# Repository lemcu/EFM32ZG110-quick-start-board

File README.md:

EFM32ZG110-quick-start-board
============================
This board is designed to be used with [LemcUSB](https://github.com/lemcu/LemcUSB), a purely software based USB peripheral for ARM Cortex M0+ devices.

Zero Gecko 110 quick start breakout board features:

1. USB support using [LemcUSB](https://github.com/lemcu/LemcUSB)
2. 31mm X 23.3mm sized board.
3. Can use either through-hole or SMD High Frequency crystal.
4. Footprint to mount an optional inductor between AVDD and VDD for Analog intensive application.
5. On board SWD Connector.
6. Onboard low noise 3.3V LDO.
7. ESD protection diodes on USB D+ D- lines.

EFM32ZG110 is chosen for presence of onchip ADC instead of EFM32ZG108.

<br />This work is licensed under a <a rel="license" href="http://creativecommons.org/licenses/by-sa/3.0/deed.en_US">Creative Commons Attribution-ShareAlike 3.0 Unported License</a>.

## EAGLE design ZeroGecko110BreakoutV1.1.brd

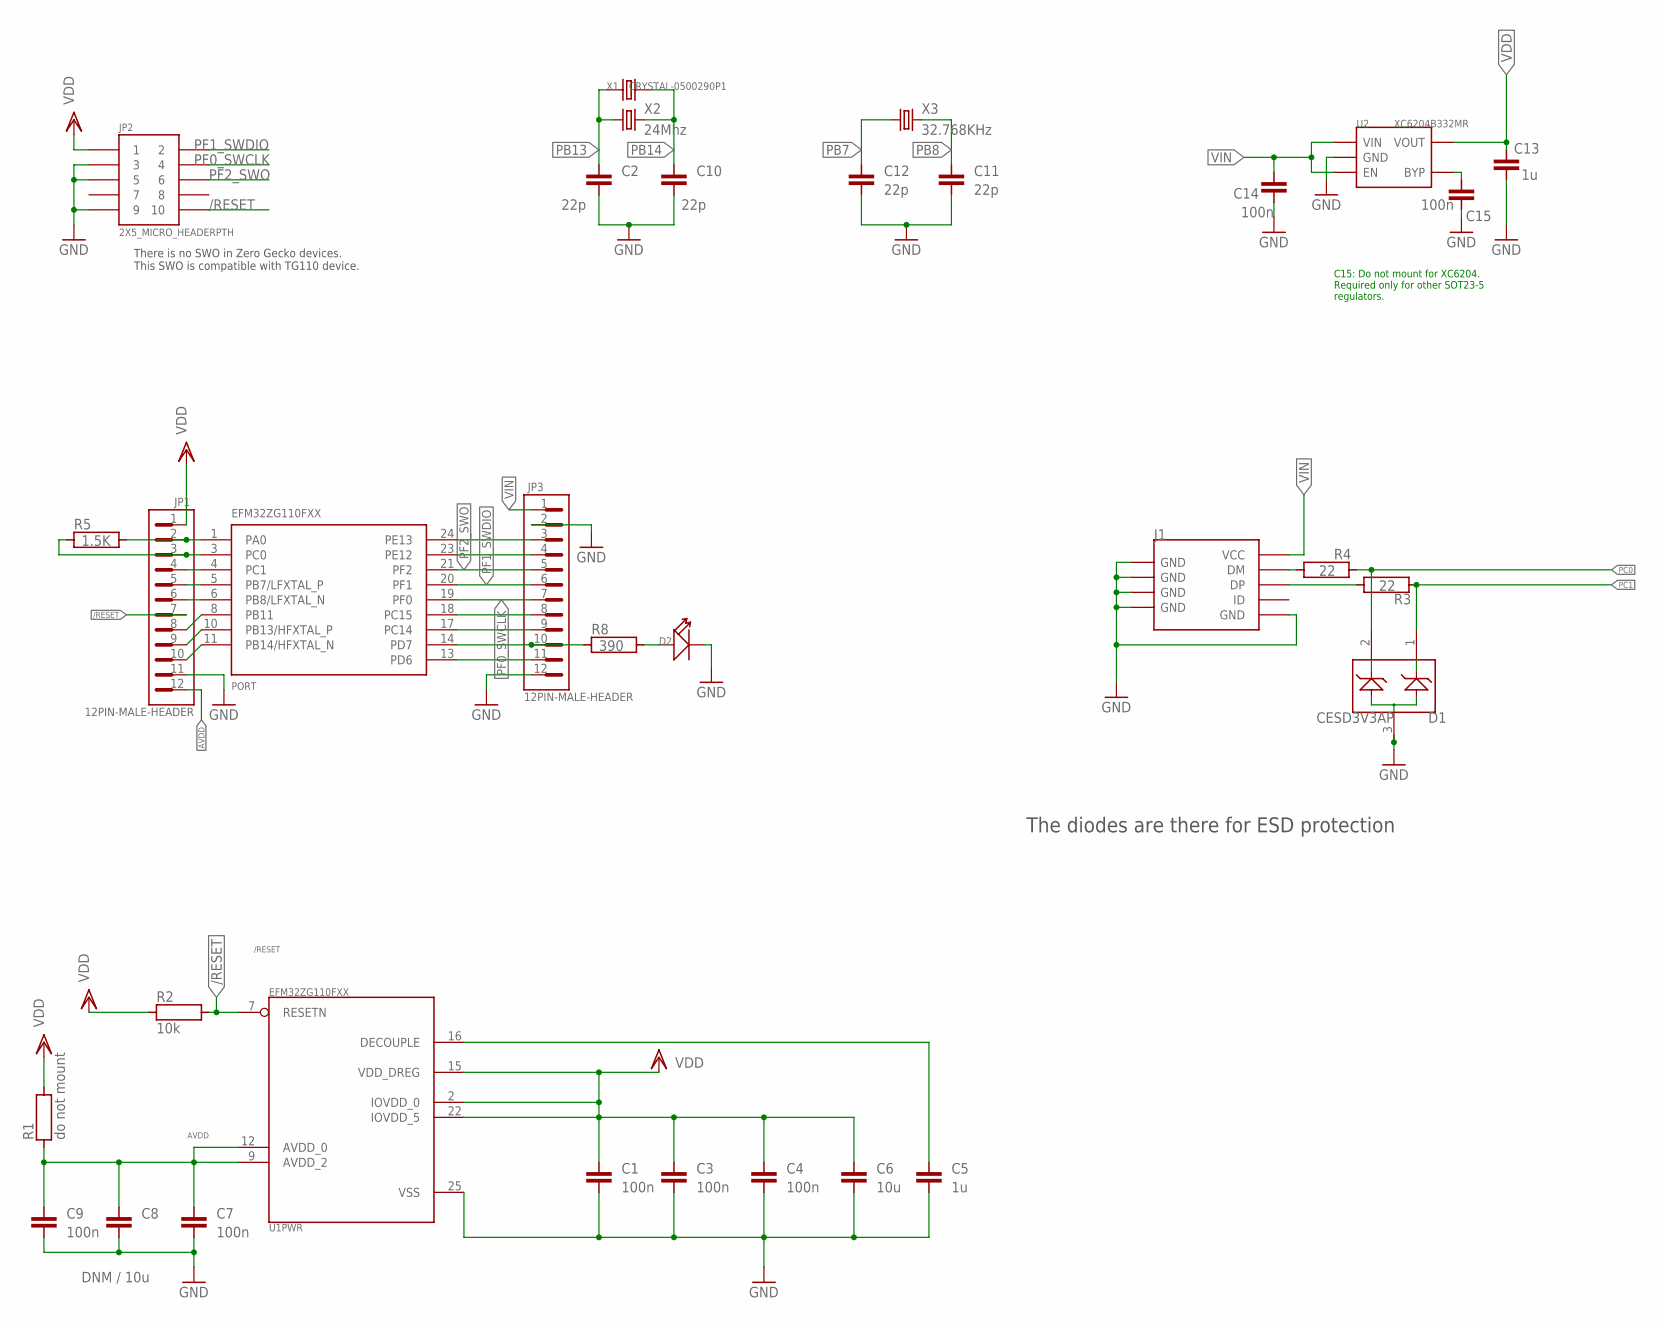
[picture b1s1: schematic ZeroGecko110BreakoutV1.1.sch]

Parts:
C1, C3, C4, C7, C9: 100n; C0603
C2, C10, C11, C12: 22p; C0603
C5, C13: 1u; C0805
C6: 10u; C0805
C8: DNM / 10u; C0805
C14, C15: 100n; C0805
D1: CESD3V3AP; SOT23
D2: LED; LED0603
J1: USB-MINIUSB-5P-MICRO; MICRO-USB
JP1, JP3: 12PIN-MALE-HEADER; 12P-2.54MM
JP2: 2X5_MICRO_HEADERPTH; 2X5_1.27MM_PTH
R1: do not mount; R0805
R2: 10k; R0603
R3, R4: 22; R0603
R5: 1.5K; R0603
R8: 390; R0603
U1: EFM32ZG110FXX; QFN24
U2: XC6204B332MR; SOT23-5
X1: CRYSTAL-0500290P1; 2P-SMD-5.0X3.2
X2: 24Mhz; HC49U-V
X3: 32.768KHz; TC26V

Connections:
/RESET: JP1.7, JP2.10, R2.2, U1.7 (RESETN)
AVDD: C7.2, C8.2, C9.2, JP1.12, R1.1, U1.9 (AVDD_2), U1.12 (AVDD_0)
GND: C1.1, C2.1, C3.1, C4.1, C5.1, C6.1, C7.1, C8.1, C9.1, C10.1, C11.1, C12.1, C13.1, C14.1, C15.1, D1.3, D2.-, J1.5 (GND), J1.S1 (GND), J1.S2 (GND), J1.S3 (GND), J1.S4 (GND), J1.S5 (GND), J1.S6 (GND), JP1.11, JP2.3, JP2.5, JP2.9, JP3.2, JP3.12, U1.25 (VSS), U2.2 (GND)
unnamed: J1.2 (DM), R4.1
unnamed: J1.3 (DP), R3.1
unnamed: D2.+, R8.2
unnamed: C15.2, U2.4 (BYP)
unnamed: C5.2, U1.16 (DECOUPLE)
PA0: JP1.2, R5.2, U1.1 (PA0)
PB7: C12.2, JP1.5, U1.5 (PB7/LFXTAL_P), X3.1
PB8: C11.2, JP1.6, U1.6 (PB8/LFXTAL_N), X3.2
PB11: JP1.8, U1.8 (PB11)
PB13: C2.2, JP1.9, U1.10 (PB13/HFXTAL_P), X1.1, X2.1
PB14: C10.2, JP1.10, U1.11 (PB14/HFXTAL_N), X1.2, X2.2
PC0: D1.2, JP1.3, R4.2, R5.1, U1.3 (PC0)
PC1: D1.1, JP1.4, R3.2, U1.4 (PC1)
PC14: JP3.9, U1.17 (PC14)
PC15: JP3.8, U1.18 (PC15)
PD6: JP3.11, U1.13 (PD6)
PD7: JP3.10, R8.1, U1.14 (PD7)
PE12: JP3.4, U1.23 (PE12)
PE13: JP3.3, U1.24 (PE13)
PF0_SWCLK: JP2.4, JP3.7, U1.19 (PF0)
PF1_SWDIO: JP2.2, JP3.6, U1.20 (PF1)
PF2_SWO: JP2.6, JP3.5, U1.21 (PF2)
VDD: C1.2, C3.2, C4.2, C6.2, C13.2, JP1.1, JP2.1, R1.2, R2.1, U1.2 (IOVDD_0), U1.15 (VDD_DREG), U1.22 (IOVDD_5), U2.5 (VOUT)
VIN: C14.2, J1.1 (VCC), JP3.1, U2.1 (VIN), U2.3 (EN)

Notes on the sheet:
There is no SWO in Zero Gecko devices. This SWO is compatible with TG110 device.
C15: Do not mount for XC6204. Required only for other SOT23-5 regulators.
The diodes are there for ESD protection

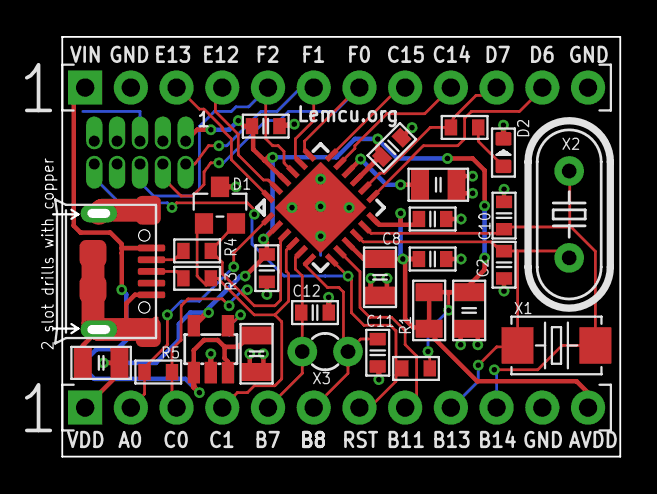
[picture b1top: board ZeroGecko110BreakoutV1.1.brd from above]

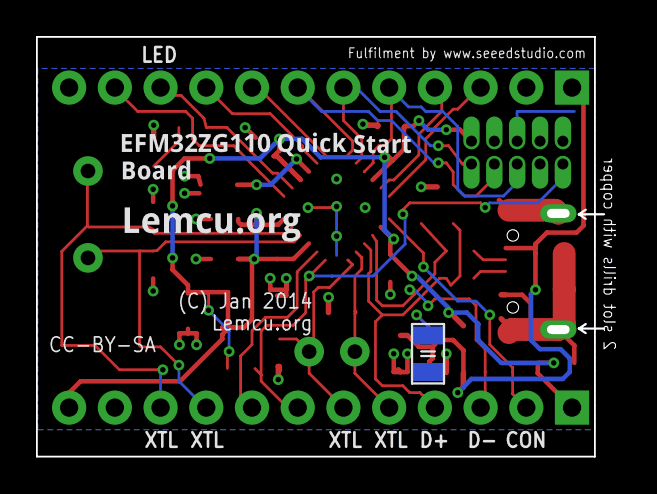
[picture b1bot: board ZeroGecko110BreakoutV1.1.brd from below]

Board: 2 copper layers, 32.0 x 22.9 mm, 32 parts (2 on the bottom side), 27 nets.

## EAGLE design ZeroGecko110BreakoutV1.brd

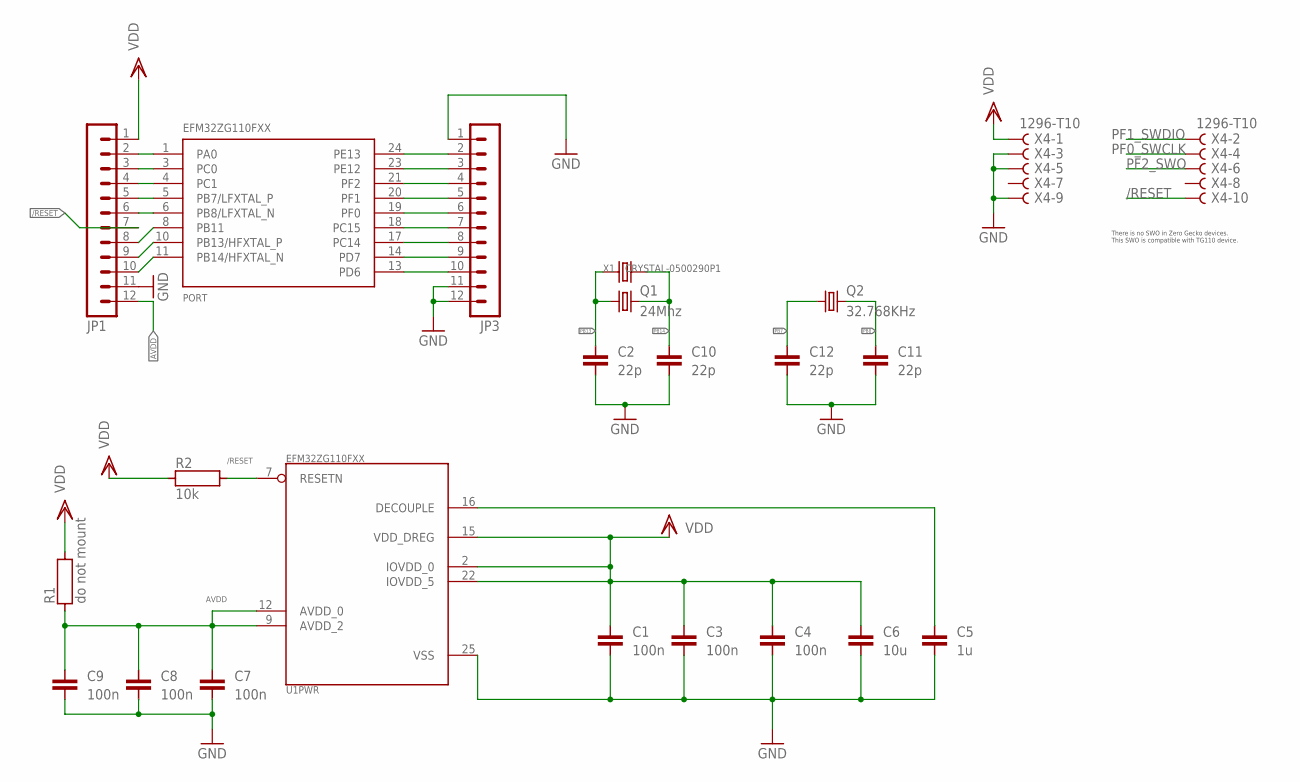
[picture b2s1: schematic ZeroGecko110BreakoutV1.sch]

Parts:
C1, C3, C4, C7, C8, C9: 100n; C0603
C2, C10, C11, C12: 22p; C0603
C5: 1u; C0805
C6: 10u; C0805
JP1, JP3: MA12-1
Q1: 24Mhz; HC49U-V
Q2: 32.768KHz; TC26V
R1: do not mount; R0805
R2: 10k; R0603
U1: EFM32ZG110FXX; QFN24
X1: CRYSTAL-0500290P1; 2P-SMD-5.0X3.2
X4: 1296-T10; 1296-10

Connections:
/RESET: JP1.7, R2.2, U1.7 (RESETN), X4.10
AVDD: C7.2, C8.2, C9.2, JP1.12, R1.1, U1.9 (AVDD_2), U1.12 (AVDD_0)
GND: C1.1, C2.1, C3.1, C4.1, C5.1, C6.1, C7.1, C8.1, C9.1, C10.1, C11.1, C12.1, JP1.11, JP3.1, JP3.11, JP3.12, U1.25 (VSS), X4.3, X4.5, X4.9
unnamed: C5.2, U1.16 (DECOUPLE)
PA0: JP1.2, U1.1 (PA0)
PB7: C12.2, JP1.5, Q2.1, U1.5 (PB7/LFXTAL_P)
PB8: C11.2, JP1.6, Q2.2, U1.6 (PB8/LFXTAL_N)
PB11: JP1.8, U1.8 (PB11)
PB13: C2.2, JP1.9, Q1.1, U1.10 (PB13/HFXTAL_P), X1.1
PB14: C10.2, JP1.10, Q1.2, U1.11 (PB14/HFXTAL_N), X1.2
PC0: JP1.3, U1.3 (PC0)
PC1: JP1.4, U1.4 (PC1)
PC14: JP3.8, U1.17 (PC14)
PC15: JP3.7, U1.18 (PC15)
PD6: JP3.10, U1.13 (PD6)
PD7: JP3.9, U1.14 (PD7)
PE12: JP3.3, U1.23 (PE12)
PE13: JP3.2, U1.24 (PE13)
PF0_SWCLK: JP3.6, U1.19 (PF0), X4.4
PF1_SWDIO: JP3.5, U1.20 (PF1), X4.2
PF2_SWO: JP3.4, U1.21 (PF2), X4.6
VDD: C1.2, C3.2, C4.2, C6.2, JP1.1, R1.2, R2.1, U1.2 (IOVDD_0), U1.15 (VDD_DREG), U1.22 (IOVDD_5), X4.1

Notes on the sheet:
There is no SWO in Zero Gecko devices. This SWO is compatible with TG110 device.

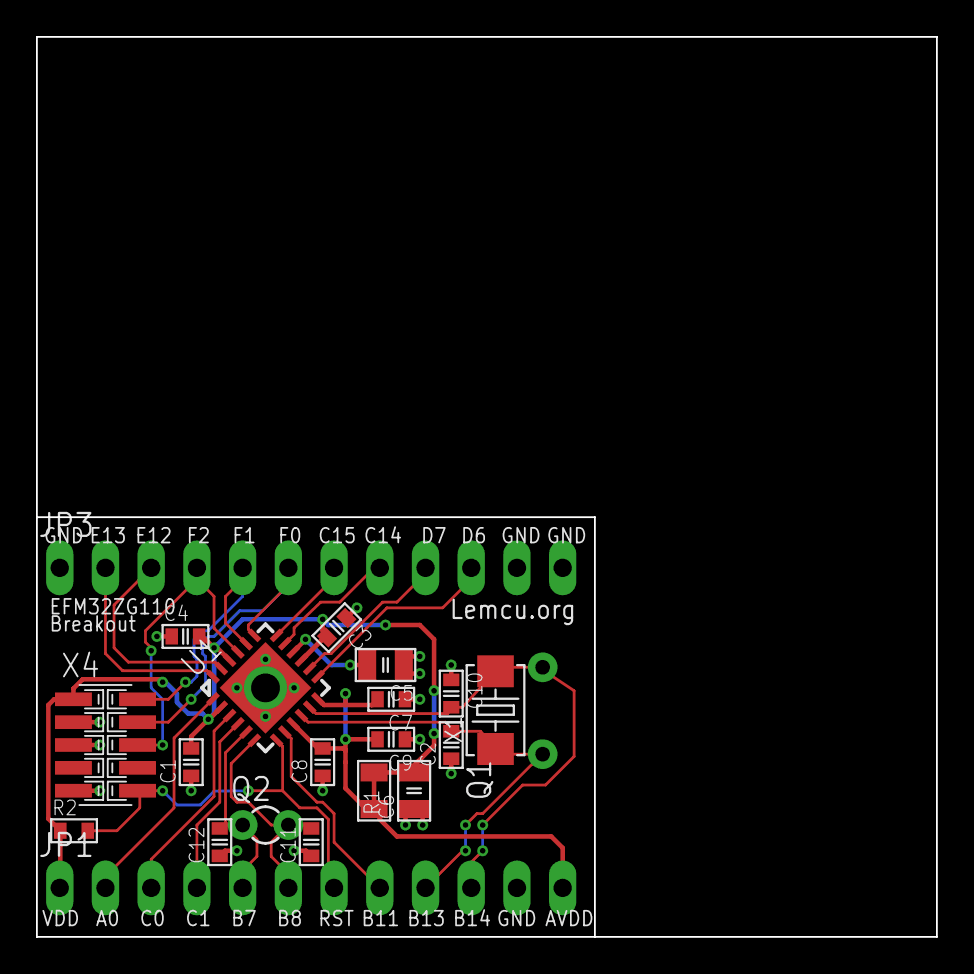
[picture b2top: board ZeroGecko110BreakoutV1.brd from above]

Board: 2 copper layers, 50.0 x 50.0 mm, 21 parts (0 on the bottom side), 22 nets.

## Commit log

2013-10-18 Schematic and Board files added
2013-10-18 Board screenshot added
2013-10-18 README.md: Screenshot link added
2013-10-18 Rendered Images
2013-10-18 Changed README filw with new image links
2013-10-19 Remove low quality screenshot image
2013-10-25 Schematic in PDF added
2014-03-21 v1.1 Release: USB support through LemcUSB firmware-only USB driver
2014-03-23 Update README.md
    Link to Software
2014-03-23 Update README.md
    Add rendered images for v1.1 PCB

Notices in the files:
ZeroGecko110BreakoutV1.1.brd:
CC-BY-SA
parts and their libraries:
ZeroGecko: CC0 License
lemcu_org_micro_pin_headers: Licensed under CC-BY-SA  or CC0
